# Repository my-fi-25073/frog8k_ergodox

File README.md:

# frog8k_ergodox
Frog 8K ergodox keyboard pcb &amp; qmk firmware

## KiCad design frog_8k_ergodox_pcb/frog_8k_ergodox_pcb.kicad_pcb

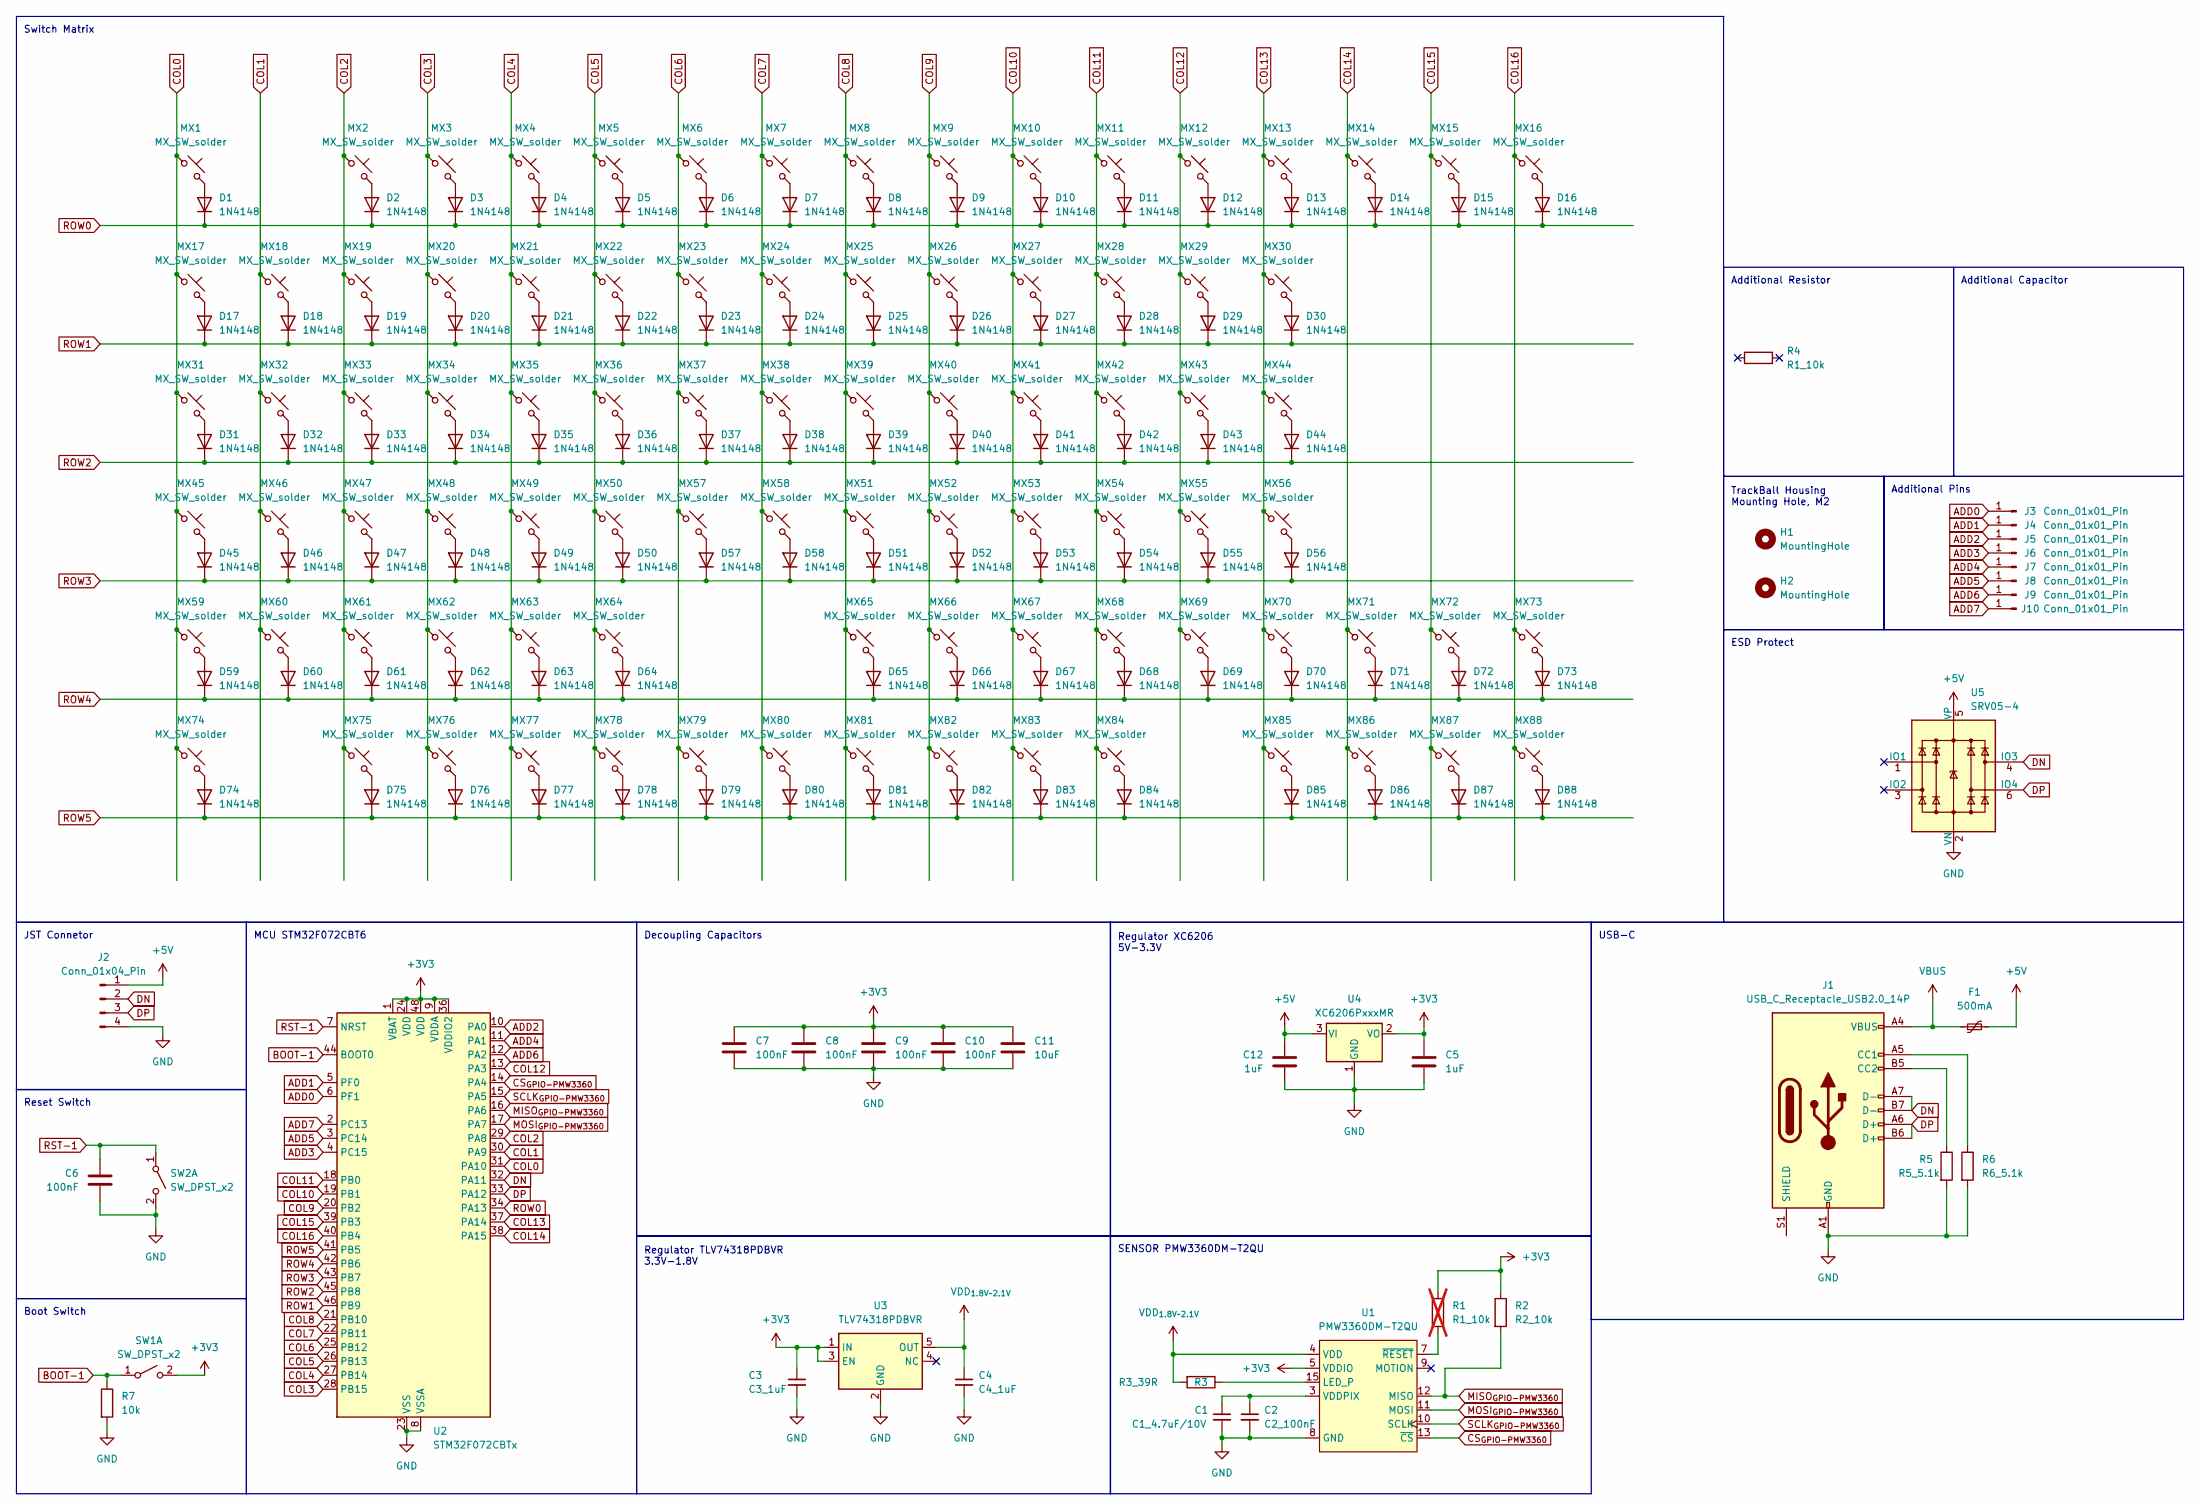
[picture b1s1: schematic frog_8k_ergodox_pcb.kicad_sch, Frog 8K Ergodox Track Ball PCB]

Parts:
C1: C1_4.7uF/10V; C_0805_2012Metric_Pad1.18x1.45mm_HandSolder
C2: C2_100nF; C_0805_2012Metric_Pad1.18x1.45mm_HandSolder
C3: C3_1uF; C_0805_2012Metric_Pad1.18x1.45mm_HandSolder
C4: C4_1uF; C_0805_2012Metric_Pad1.18x1.45mm_HandSolder
C5, C12: 1uF; C_0402_1005Metric
C6, C7, C8, C9, C10: 100nF; C_0402_1005Metric
C11: 10uF; C_0402_1005Metric
D1, D2, D3, D4, D5, D6, D7, D8, D9, D10, D11, D12, D13, D14, D15, D16, D17, D18, D19, D20, D21, D22, D23, D24, D25, D26, D27, D28, D29, D30, D31, D32, D33, D34, D35, D36, D37, D38, D39, D40, D41, D42, D43, D44, D45, D46, D47, D48, D49, D50, D51, D52, D53, D54, D55, D56, D57, D58, D59, D60, D61, D62, D63, D64, D65, D66, D67, D68, D69, D70, D71, D72, D73, D74, D75, D76, D77, D78, D79, D80, D81, D82, D83, D84, D85, D86, D87, D88: 1N4148; D_SOD-123
F1: 500mA; Fuse_1206_3216Metric; LCSC C70076
H1: MountingHole; MountingHole_2.2mm_M2_ISO14580_Pad
H2: MountingHole; MountingHole_2.2mm_M2_ISO7380_Pad
J1: USB_C_Receptacle_USB2.0_14P; USB_C_Receptacle_HRO_TYPE-C-31-M-12
J2: Conn_01x04_Pin; JST_SH_SM04B-SRSS-TB_1x04-1MP_P1.00mm_Horizontal
J3, J4, J5, J6, J7, J8, J9, J10: Conn_01x01_Pin; TestPoint_Pad_1.5x1.5mm
MX1, MX2, MX3, MX4, MX5, MX6, MX7, MX8, MX9, MX10, MX11, MX12, MX13, MX14, MX15, MX16, MX17, MX18, MX19, MX20, MX21, MX22, MX23, MX24, MX25, MX26, MX27, MX28, MX29, MX30, MX31, MX32, MX33, MX34, MX35, MX36, MX37, MX38, MX39, MX40, MX41, MX42, MX43, MX44, MX45, MX46, MX47, MX48, MX49, MX50, MX51, MX52, MX53, MX54, MX55, MX56, MX57, MX58, MX59, MX60, MX61, MX62, MX63, MX64, MX65, MX66, MX67, MX68, MX69, MX70, MX71, MX72, MX73, MX74, MX75, MX76, MX77, MX78, MX79, MX80, MX81, MX82, MX83, MX84, MX85, MX86, MX87, MX88: MX_SW_solder; SW_MX_1u
R1: R1_10k; R_0805_2012Metric_Pad1.20x1.40mm_HandSolder; not fitted
R2: R2_10k; R_0805_2012Metric_Pad1.20x1.40mm_HandSolder
R3: R3_39R; R_0805_2012Metric_Pad1.20x1.40mm_HandSolder
R4: R1_10k; R_0805_2012Metric_Pad1.20x1.40mm_HandSolder
R5: R5_5.1k; R_0805_2012Metric_Pad1.20x1.40mm_HandSolder
R6: R6_5.1k; R_0805_2012Metric_Pad1.20x1.40mm_HandSolder
R7: 10k; R_0402_1005Metric
SW1, SW2: SW_DPST_x2; SW_Push_1P1T_XKB_TS-1187A
U1: PMW3360DM-T2QU; PMW3360DM-T2QU 16Pin
U2: STM32F072CBTx; LQFP-48_7x7mm_P0.5mm
U3: TLV74318PDBVR; SOT-23-5
U4: XC6206PxxxMR; SOT-23-3
U5: SRV05-4; SOT-23-6

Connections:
+3V3: C3.1, C5.1, C7.1, C8.1, C9.1, C10.1, C11.1, R1.1, R2.1, SW1.2 (B), U1.5 (VDDIO), U2.1 (VBAT), U2.9 (VDDA), U2.24 (VDD), U2.36 (VDDIO2), U2.48 (VDD), U3.1 (IN), U3.3 (EN), U4.2 (VO)
+5V: C12.1, F1.2, J2.1, U4.3 (VI), U5.5 (VP)
ADD0: J3.1, U2.6 (PF1)
ADD1: J4.1, U2.5 (PF0)
ADD2: J5.1, U2.10 (PA0)
ADD3: J6.1, U2.4 (PC15)
ADD4: J7.1, U2.11 (PA1)
ADD5: J8.1, U2.3 (PC14)
ADD6: J9.1, U2.12 (PA2)
ADD7: J10.1, U2.2 (PC13)
BOOT-1: R7.1, SW1.1 (A), U2.44 (BOOT0)
COL0: MX1.1, MX17.1, MX31.1, MX45.1, MX59.1, MX74.1, U2.31 (PA10)
COL1: MX18.1, MX32.1, MX46.1, MX60.1, U2.30 (PA9)
COL2: MX2.1, MX19.1, MX33.1, MX47.1, MX61.1, MX75.1, U2.29 (PA8)
COL3: MX3.1, MX20.1, MX34.1, MX48.1, MX62.1, MX76.1, U2.28 (PB15)
COL4: MX4.1, MX21.1, MX35.1, MX49.1, MX63.1, MX77.1, U2.27 (PB14)
COL5: MX5.1, MX22.1, MX36.1, MX50.1, MX64.1, MX78.1, U2.26 (PB13)
COL6: MX6.1, MX23.1, MX37.1, MX57.1, MX79.1, U2.25 (PB12)
COL7: MX7.1, MX24.1, MX38.1, MX58.1, MX80.1, U2.22 (PB11)
COL8: MX8.1, MX25.1, MX39.1, MX51.1, MX65.1, MX81.1, U2.21 (PB10)
COL9: MX9.1, MX26.1, MX40.1, MX52.1, MX66.1, MX82.1, U2.20 (PB2)
COL10: MX10.1, MX27.1, MX41.1, MX53.1, MX67.1, MX83.1, U2.19 (PB1)
COL11: MX11.1, MX28.1, MX42.1, MX54.1, MX68.1, MX84.1, U2.18 (PB0)
COL12: MX12.1, MX29.1, MX43.1, MX55.1, MX69.1, U2.13 (PA3)
COL13: MX13.1, MX30.1, MX44.1, MX56.1, MX70.1, MX85.1, U2.37 (PA14)
COL14: MX14.1, MX71.1, MX86.1, U2.38 (PA15)
COL15: MX15.1, MX72.1, MX87.1, U2.39 (PB3)
COL16: MX16.1, MX73.1, MX88.1, U2.40 (PB4)
CS_{GPIO-PMW3360}: U1.13 (~CS), U2.14 (PA4)
DN: J1.A7 (D-), J1.B7 (D-), J2.2, U2.32 (PA11), U5.4 (IO3)
DP: J1.A6 (D+), J1.B6 (D+), J2.3, U2.33 (PA12), U5.6 (IO4)
GND: C1.2, C2.2, C3.2, C4.2, C5.2, C6.2, C7.2, C8.2, C9.2, C10.2, C11.2, C12.2, J1.A1 (GND), J1.A12 (GND), J1.B1 (GND), J1.B12 (GND), J2.4, R5.2, R6.2, R7.2, SW2.2 (B), U1.8 (GND), U2.8 (VSSA), U2.23 (VSS), U2.35 (VSS), U2.47 (VSS), U3.2 (GND), U4.1 (GND), U5.2 (VN)
MISO_{GPIO-PMW3360}: R2.2, U1.12 (MISO), U2.16 (PA6)
MOSI_{GPIO-PMW3360}: U1.11 (MOSI), U2.17 (PA7)
unnamed: D1.2 (A), MX1.2
unnamed: D2.2 (A), MX2.2
unnamed: D3.2 (A), MX3.2
unnamed: D4.2 (A), MX4.2
unnamed: D5.2 (A), MX5.2
unnamed: D6.2 (A), MX6.2
unnamed: D7.2 (A), MX7.2
unnamed: D8.2 (A), MX8.2
unnamed: D9.2 (A), MX9.2
unnamed: D10.2 (A), MX10.2
unnamed: D11.2 (A), MX11.2
unnamed: D12.2 (A), MX12.2
unnamed: D13.2 (A), MX13.2
unnamed: D14.2 (A), MX14.2
unnamed: D15.2 (A), MX15.2
unnamed: D16.2 (A), MX16.2
unnamed: D17.2 (A), MX17.2
unnamed: D18.2 (A), MX18.2
unnamed: D19.2 (A), MX19.2
unnamed: D20.2 (A), MX20.2
unnamed: D21.2 (A), MX21.2
unnamed: D22.2 (A), MX22.2
unnamed: D23.2 (A), MX23.2
unnamed: D24.2 (A), MX24.2
unnamed: D25.2 (A), MX25.2
unnamed: D26.2 (A), MX26.2
unnamed: D27.2 (A), MX27.2
unnamed: D28.2 (A), MX28.2
unnamed: D29.2 (A), MX29.2
unnamed: D30.2 (A), MX30.2
unnamed: D31.2 (A), MX31.2
unnamed: D32.2 (A), MX32.2
unnamed: D33.2 (A), MX33.2
unnamed: D34.2 (A), MX34.2
unnamed: D35.2 (A), MX35.2
unnamed: D36.2 (A), MX36.2
unnamed: D37.2 (A), MX37.2
unnamed: D38.2 (A), MX38.2
unnamed: D39.2 (A), MX39.2
unnamed: D40.2 (A), MX40.2
unnamed: D41.2 (A), MX41.2
unnamed: D42.2 (A), MX42.2
unnamed: D43.2 (A), MX43.2
unnamed: D44.2 (A), MX44.2
unnamed: D45.2 (A), MX45.2
unnamed: D46.2 (A), MX46.2
unnamed: D47.2 (A), MX47.2
unnamed: D48.2 (A), MX48.2
unnamed: D49.2 (A), MX49.2
unnamed: D50.2 (A), MX50.2
unnamed: D51.2 (A), MX51.2
unnamed: D52.2 (A), MX52.2
unnamed: D53.2 (A), MX53.2
unnamed: D54.2 (A), MX54.2
unnamed: D55.2 (A), MX55.2
unnamed: D56.2 (A), MX56.2
unnamed: D57.2 (A), MX57.2
unnamed: D58.2 (A), MX58.2
unnamed: D59.2 (A), MX59.2
unnamed: D60.2 (A), MX60.2
unnamed: D61.2 (A), MX61.2
unnamed: D62.2 (A), MX62.2
unnamed: D63.2 (A), MX63.2
unnamed: D64.2 (A), MX64.2
unnamed: D65.2 (A), MX65.2
unnamed: D66.2 (A), MX66.2
unnamed: D67.2 (A), MX67.2
unnamed: D68.2 (A), MX68.2
unnamed: D69.2 (A), MX69.2
unnamed: D70.2 (A), MX70.2
unnamed: D71.2 (A), MX71.2
unnamed: D72.2 (A), MX72.2
unnamed: D73.2 (A), MX73.2
unnamed: D74.2 (A), MX74.2
unnamed: D75.2 (A), MX75.2
unnamed: D76.2 (A), MX76.2
unnamed: D77.2 (A), MX77.2
unnamed: D78.2 (A), MX78.2
unnamed: D79.2 (A), MX79.2
unnamed: D80.2 (A), MX80.2
unnamed: D81.2 (A), MX81.2
unnamed: D82.2 (A), MX82.2
unnamed: D83.2 (A), MX83.2
unnamed: D84.2 (A), MX84.2
unnamed: D85.2 (A), MX85.2
unnamed: D86.2 (A), MX86.2
unnamed: D87.2 (A), MX87.2
unnamed: D88.2 (A), MX88.2
unnamed: J1.A5 (CC1), R6.1
unnamed: J1.B5 (CC2), R5.1
unnamed: R3.1, U1.15 (LED_P)
unnamed: C1.1, C2.1, U1.3 (VDDPIX)
unnamed: R1.2, U1.7 (~RESET)
ROW0: D1.1 (K), D2.1 (K), D3.1 (K), D4.1 (K), D5.1 (K), D6.1 (K), D7.1 (K), D8.1 (K), D9.1 (K), D10.1 (K), D11.1 (K), D12.1 (K), D13.1 (K), D14.1 (K), D15.1 (K), D16.1 (K), U2.34 (PA13)
ROW1: D17.1 (K), D18.1 (K), D19.1 (K), D20.1 (K), D21.1 (K), D22.1 (K), D23.1 (K), D24.1 (K), D25.1 (K), D26.1 (K), D27.1 (K), D28.1 (K), D29.1 (K), D30.1 (K), U2.46 (PB9)
ROW2: D31.1 (K), D32.1 (K), D33.1 (K), D34.1 (K), D35.1 (K), D36.1 (K), D37.1 (K), D38.1 (K), D39.1 (K), D40.1 (K), D41.1 (K), D42.1 (K), D43.1 (K), D44.1 (K), U2.45 (PB8)
ROW3: D45.1 (K), D46.1 (K), D47.1 (K), D48.1 (K), D49.1 (K), D50.1 (K), D51.1 (K), D52.1 (K), D53.1 (K), D54.1 (K), D55.1 (K), D56.1 (K), D57.1 (K), D58.1 (K), U2.43 (PB7)
ROW4: D59.1 (K), D60.1 (K), D61.1 (K), D62.1 (K), D63.1 (K), D64.1 (K), D65.1 (K), D66.1 (K), D67.1 (K), D68.1 (K), D69.1 (K), D70.1 (K), D71.1 (K), D72.1 (K), D73.1 (K), U2.42 (PB6)
ROW5: D74.1 (K), D75.1 (K), D76.1 (K), D77.1 (K), D78.1 (K), D79.1 (K), D80.1 (K), D81.1 (K), D82.1 (K), D83.1 (K), D84.1 (K), D85.1 (K), D86.1 (K), D87.1 (K), D88.1 (K), U2.41 (PB5)
RST-1: C6.1, SW2.1 (A), U2.7 (NRST)
SCLK_{GPIO-PMW3360}: U1.10 (SCLK), U2.15 (PA5)
VBUS: F1.1, J1.A4 (VBUS), J1.A9 (VBUS), J1.B4 (VBUS), J1.B9 (VBUS)
VDD_{1.8V~2.1V}: C4.1, R3.2, U1.4 (VDD), U3.5 (OUT)

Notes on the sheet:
TrackBall Housing Mounting Hole, M2
Regulator XC6206 5V-3.3V
Additional Pins
USB-C
SENSOR PMW3360DM-T2QU
Switch Matrix
Regulator TLV74318PDBVR 3.3V-1.8V
Decoupling Capacitors
Additional Resistor
MCU STM32F072CBT6
JST Connetor
Reset Switch
ESD Protect
Additional Capacitor
Boot Switch

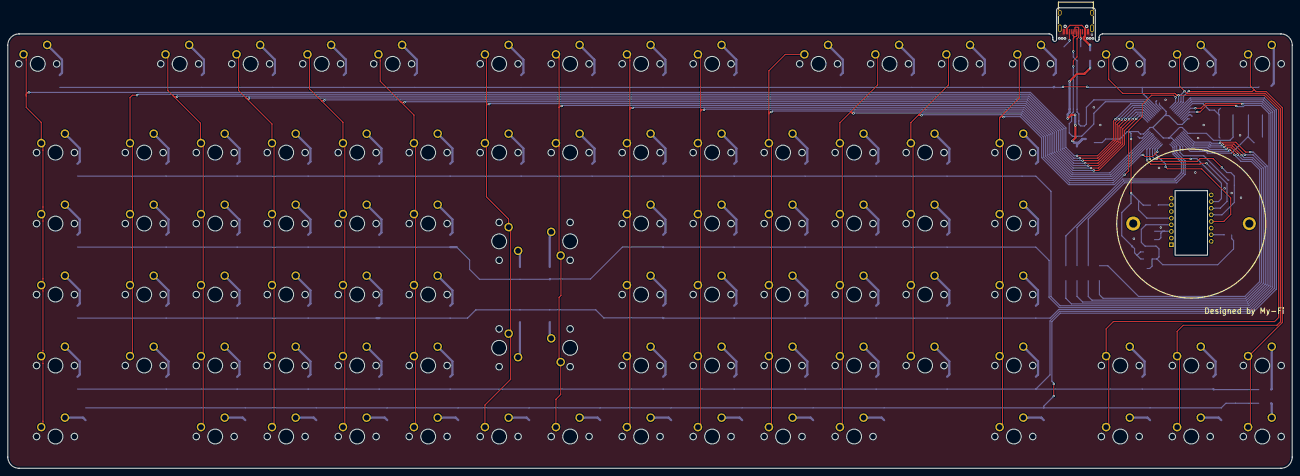
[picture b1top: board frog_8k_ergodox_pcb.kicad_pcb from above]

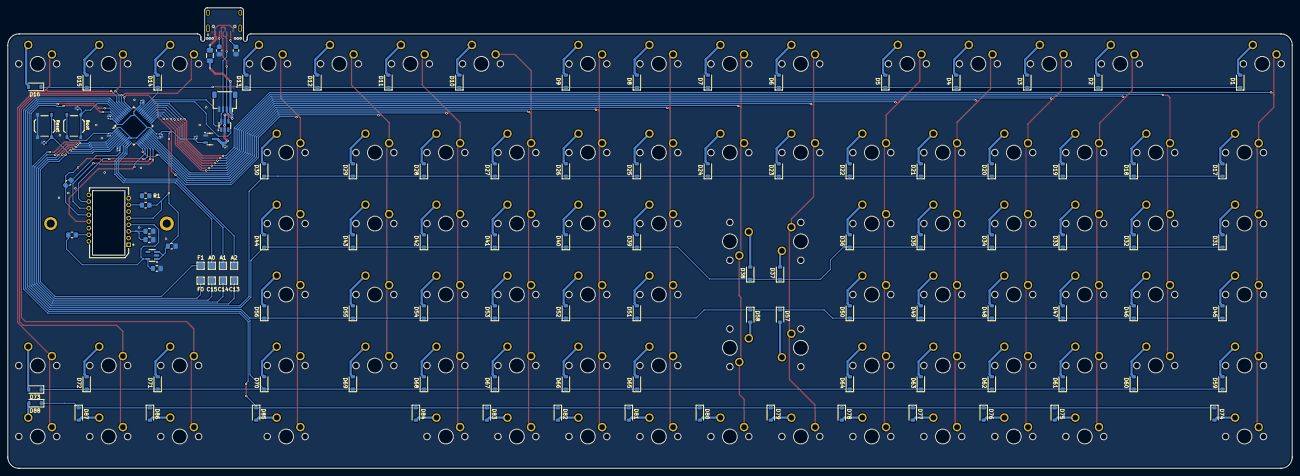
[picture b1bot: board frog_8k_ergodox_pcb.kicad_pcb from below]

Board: 2 copper layers, 344.7 x 123.6 mm, 217 parts (124 on the bottom side), 137 nets.

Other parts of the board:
mouse-bite-custom: VAL**; mouse-bite-custom
mouse-bite-custom#2: VAL**; mouse-bite-custom

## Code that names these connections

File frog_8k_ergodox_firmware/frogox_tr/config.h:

#pragma once

// https://docs.qmk.fm/drivers/spi
// SPI Pins for PMW3360 - STM32F072

// https://www.st.com/resource/en/datasheet/stm32f072cb.pdf
// 38 page

//  PA4 - GPIO (CS)
//  PA6 - SPI1_MISO
//  PA7 - SPI1_MOSI
//  PA5 - SPI1_SCK

#define SPI_SCK_PAL_MODE 0
#define SPI_MISO_PAL_MODE 0
#define SPI_MOSI_PAL_MODE 0

#define PMW33XX_CS_PIN A4 // SPI CS pin.
#define SPI_SCK_PIN A5
#define SPI_MISO_PIN A6
#define SPI_MOSI_PIN A7

#define POINTING_DEVICE_INVERT_Y

#define DYNAMIC_KEYMAP_LAYER_COUNT 6

/* Optional. */
#define PMW33XX_CPI 900             // The CPI range is 100-12000, in increments of 100. Defaults to 1600 CPI.
#define PMW33XX_CLOCK_SPEED 2000000 // Sets the clock speed that the sensor runs at. Defaults to 2000000
#define MOUSE_EXTENDED_REPORT       // Use -32767 to 32767, instead of just -127 to 127.
#define WHEEL_EXTENDED_REPORT       // Use -32767 to 32767, instead of just -127 to 127.


// #define PMW33XX_SPI_DIVISOR
// #define POINTING_DEVICE_TASK_THROTTLE_MS 10

// https://docs.qmk.fm/features/pointing_device

// Addintion GPIO Pins for keyboard

// ADD0 - F1
// ADD1 - F0
// ADD2 - A0
// ADD3 - C15
// ADD4 - A1
// ADD5 - C14
// ADD6 - A2
// ADD7 - C13

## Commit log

2025-03-02 Added Default pcb project files
2025-03-03 Added PMW3360 FP&Symbol
2025-03-03 Updated Symbols
2025-03-04 Added 3v3 power and gnd symbol
2025-03-05 Updated Capcitors and circuits for PMW3360
2025-03-06 Connected pmw3360 to stm32
2025-03-12 Updated PMW3360's GPIO Pin.
2025-03-13 Removed unused symbol in PMW3360, Added Regulator for PCB
2025-03-24 Added Trackball Cover STL model made by HYT
2025-03-24 Added Switches and JST connector.
2025-03-26 Updated Matrix & Col2Row Based Diodes.
2025-03-27 Added Pull Up Resistor Symbol on PMW3360 NRESET Pin, Added ESD Protection.
2025-03-30 Added fuse to vbus.
2025-04-03 Added Keyboard Layout on PCB design
2025-04-03 Rotated middle keys.
2025-04-04 Updated USB-C Position, Added PCB Edge Cut
2025-04-06 Updated TrackBall Housing Position & Mounting Hole Position.
2025-04-07 Fixed matirix, Reconnect U1 Symbol to Footprint, relocate diode position.
2025-04-07 Updated PCB design.
2025-04-08 Fixed USB Port 5V to 3.3V, Added Matrix Row/Col
2025-04-09 Added plate file, Updated Matrix route, Additional Pin routes
2025-04-09 updated footprints...
2025-04-10 Added First version of qmk firmware with trackball
2025-04-10 Connect PMW3360 pins.
2025-04-11 Connected All nets.
2025-04-11 fixed connection little bit
2025-04-12 Connect and fill ground.
2025-04-12 Almost Done with pcb
2025-04-13 Released V1.0.00
2025-04-13 Updated GPIO pins & Added release v1.0.00 firmware
2025-04-22 Updated config.h
